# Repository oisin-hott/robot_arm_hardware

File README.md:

# robot_arm_hardware
folder with my CAD and electonics work for the robot arm.

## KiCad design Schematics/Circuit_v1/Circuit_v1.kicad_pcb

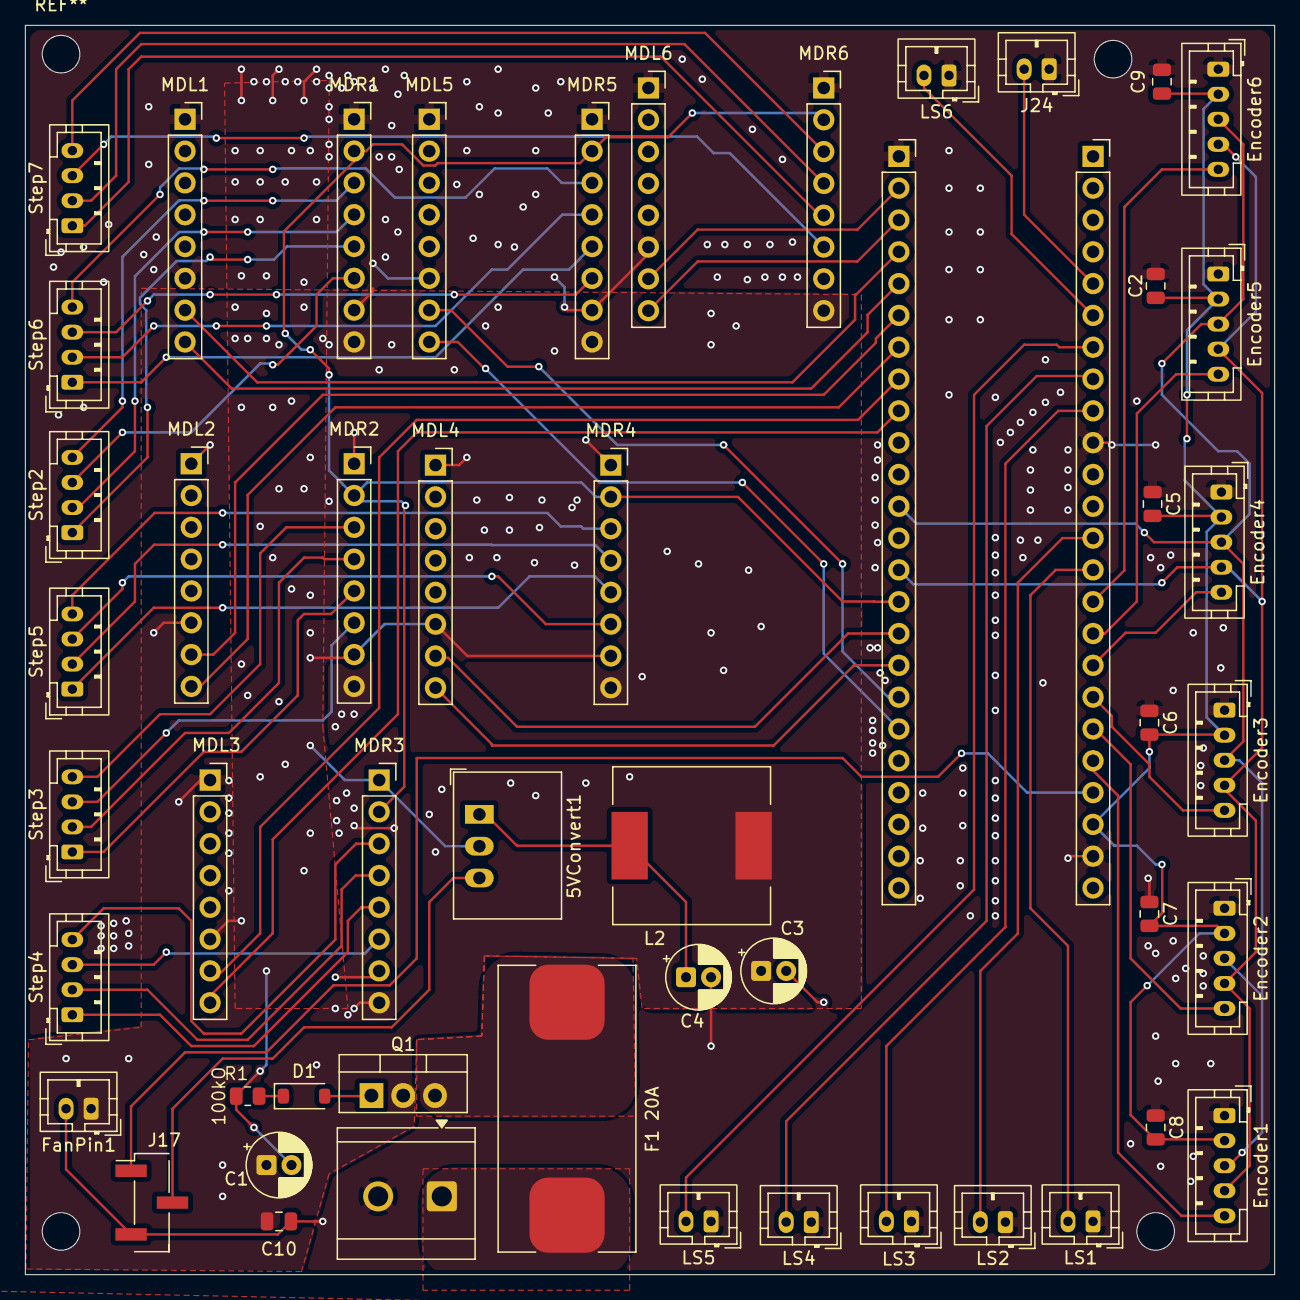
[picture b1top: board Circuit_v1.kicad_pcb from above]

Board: 2 copper layers, 99.8 x 99.8 mm, 52 parts (0 on the bottom side), 62 nets.

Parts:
5VConvert1: R-78E5.0-1.0; Converter_DCDC_RECOM_R-78E-0.5_THT
C1: 10uF; CP_Radial_D5.0mm_P2.00mm
C2, C5, C6, C7, C8, C9, C10: 0.1uF; C_0805_2012Metric
C3: 10uf; CP_Radial_D5.0mm_P2.00mm
C4: 4.7uf; CP_Radial_D5.0mm_P2.00mm
D1: D_Zener; D_SOD-123
Encoder1, Encoder2, Encoder3, Encoder4, Encoder5, Encoder6: Conn_01x05_Socket; JST_PH_B5B-PH-K_1x05_P2.00mm_Vertical
F1: 20A; Fuseholder_Cylinder-5x20mm_Schurter_OGN-SMD_Horizontal_Open
FanPin1: Conn_01x02_Pin; JST_PH_B2B-PH-K_1x02_P2.00mm_Vertical
J15: Teensy; PinSocket_1x24_P2.54mm_Vertical
J16: TeensyRHS; PinSocket_1x24_P2.54mm_Vertical
J17: Servo Pin; PinHeader_1x03_P2.54mm_Vertical_SMD_Pin1Left
J24: Conn_01x02_Socket; JST_PH_B2B-PH-K_1x02_P2.00mm_Vertical
L2: 12uH; L_12x12mm_H8mm
LS1, LS2, LS3, LS4, LS5, LS6: Conn_01x02_Socket; JST_PH_B2B-PH-K_1x02_P2.00mm_Vertical
MDL1, MDL2, MDL3, MDL4, MDL5, MDL6: Conn_01x08_Socket; PinSocket_1x08_P2.54mm_Vertical
MDR1, MDR2, MDR3, MDR4, MDR5, MDR6: Conn_01x08_Socket; PinSocket_1x08_P2.54mm_Vertical
P_IN1: Screw_Terminal_01x02; TerminalBlock_CUI_TB007-508-02_1x02_P5.08mm_Horizontal
Q1: Q_PMOS_GSD; TO-220-3_Vertical
R1: 100kO; R_0805_2012Metric
Step2, Step3, Step4, Step5, Step6, Step7: Conn_01x04; JST_PH_B4B-PH-K_1x04_P2.00mm_Vertical

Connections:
+24V: C1.1, C3.1, C10.1, FanPin1.1, L2.1, MDR1.8, MDR2.8, MDR3.8, MDR4.8, MDR5.8, MDR6.8, Q1.2 (S)
GND: 5VConvert1.2 (GND), C1.2, C2.1, C3.2, C4.2, C5.1, C6.1, C7.1, C8.1, C9.1, C10.2, Encoder1.1, Encoder2.1, Encoder3.1, Encoder4.1, Encoder5.1, Encoder6.1, FanPin1.2, J15.1, J16.10, J16.23, J17.3, J24.1, LS1.1, LS2.1, LS3.1, LS4.1, LS5.1, LS6.1, MDL1.1, MDL1.6, MDL2.1, MDL2.6, MDL3.1, MDL3.6, MDL4.1, MDL4.6, MDL5.1, MDL5.6, MDL6.1, MDL6.6, MDR1.1, MDR1.7, MDR2.1, MDR2.7, MDR3.1, MDR3.7, MDR4.1, MDR4.7, MDR5.1, MDR5.7, MDR6.1, MDR6.7, P_IN1.2, R1.1
unnamed: 5VConvert1.1 (IN), C4.1, L2.2
unnamed: 5VConvert1.3 (OUT), J17.2
unnamed: D1.2 (A), Q1.1 (G)
unnamed: D1.1 (K), R1.2
unnamed: C2.2, C5.2, C6.2, C7.2, C8.2, C9.2, Encoder1.2, Encoder2.2, Encoder3.2, Encoder4.2, Encoder5.2, Encoder6.2, J16.22
unnamed: Encoder1.3, Encoder2.3, Encoder3.3, Encoder4.3, Encoder5.3, Encoder6.3, J15.12
unnamed: Encoder1.4, Encoder2.4, Encoder3.4, Encoder4.4, Encoder5.4, Encoder6.4, J15.14
unnamed: Encoder1.5, J16.20
unnamed: Encoder2.5, J16.19
unnamed: Encoder3.5, J16.18
unnamed: Encoder4.5, J16.17
unnamed: Encoder5.5, J16.16
unnamed: Encoder6.5, J16.15
unnamed: J15.2, MDL6.7
unnamed: J15.3, MDL6.8
unnamed: J15.4, MDL1.7
unnamed: J15.5, MDL1.8
unnamed: J15.6, MDL2.7
unnamed: J15.7, MDL2.8
unnamed: J15.8, MDL3.7
unnamed: J15.9, MDL3.8
unnamed: J15.15, MDR1.2, MDR2.2, MDR3.2, MDR4.2, MDR5.2, MDR6.2
unnamed: J15.16, MDL4.7
unnamed: J15.17, MDL4.8
unnamed: J15.18, MDL5.7
unnamed: J15.19, MDL5.8
unnamed: J16.5, J24.2
unnamed: J16.6, LS6.2
unnamed: J16.7, LS5.2
unnamed: J16.8, LS4.2
unnamed: J16.9, LS3.2
unnamed: J16.13, LS2.2
unnamed: J16.14, LS1.2
unnamed: J16.21, J17.1
unnamed: F1.2, P_IN1.1
unnamed: F1.1, Q1.3 (D)
unnamed: MDR1.5, Step2.1
unnamed: MDR1.4, Step2.2
unnamed: MDR1.6, Step2.3
unnamed: MDR1.3, Step2.4
unnamed: MDR2.5, Step3.1
unnamed: MDR2.4, Step3.2
unnamed: MDR2.6, Step3.3
unnamed: MDR2.3, Step3.4
unnamed: MDR3.5, Step4.1
unnamed: MDR3.4, Step4.2
unnamed: MDR3.6, Step4.3
unnamed: MDR3.3, Step4.4
unnamed: MDR4.5, Step5.1
unnamed: MDR4.4, Step5.2
unnamed: MDR4.6, Step5.3
unnamed: MDR4.3, Step5.4
unnamed: MDR5.5, Step6.1
unnamed: MDR5.4, Step6.2
unnamed: MDR5.6, Step6.3
unnamed: MDR5.3, Step6.4
unnamed: MDR6.5, Step7.1
unnamed: MDR6.4, Step7.2
unnamed: MDR6.6, Step7.3
unnamed: MDR6.3, Step7.4
